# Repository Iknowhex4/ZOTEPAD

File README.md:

# ZOTEPAD

## About
This is my Zotepad it was named for Zote The Mighty from the hit indie Game 'Hollow Knight'. The Macropad has 6 keys and a rotary encoder. I designed the keys to be the battle keybinds for 'Undertale', so I can finally beat the boss Undyne the Undying. The case is a standard sandwich mount in which the PCB hangs of the top plate. The case is held together with heat set inserts and screws. I used KMK firmware to code the mapping of the keys. The case was made in onshape and the PCB has some silkcreen on it depicting the character 'Zote the Mighty'. I couldn't figure out how to hide the screws on the case; I could tell it was by flipping them upside down, but I didn't want to focus on that for my project. I found the hardest part of the project to be using CAD software for design, but after messing around a bit with the controls I figured out how to do it. I followed the guide for the begining making the PCB etc, but I stopped using it when I went back to the schematics to add my own features. 
## BOM
- 1x Zotepad Pcb
- 1x Bottom Case
- 1x Top Plate
- 6x MX Switches
- 1x Rotary Encoder EC11
- 1x XIAO RP2040
- 6x White Blank DSA keycaps
- 4x M3x16mm screws
- 4x M3x5mx4mm heatset inserts

This is my CAD link:
https://cad.onshape.com/documents/b8c557c7cba29d893ec7ee97/w/a27e70a122ce197b2fa20963/e/21f0d5da1cc23e3e0d761768?renderMode=0&uiState=6ac2b3909b3a99bbd460e99a

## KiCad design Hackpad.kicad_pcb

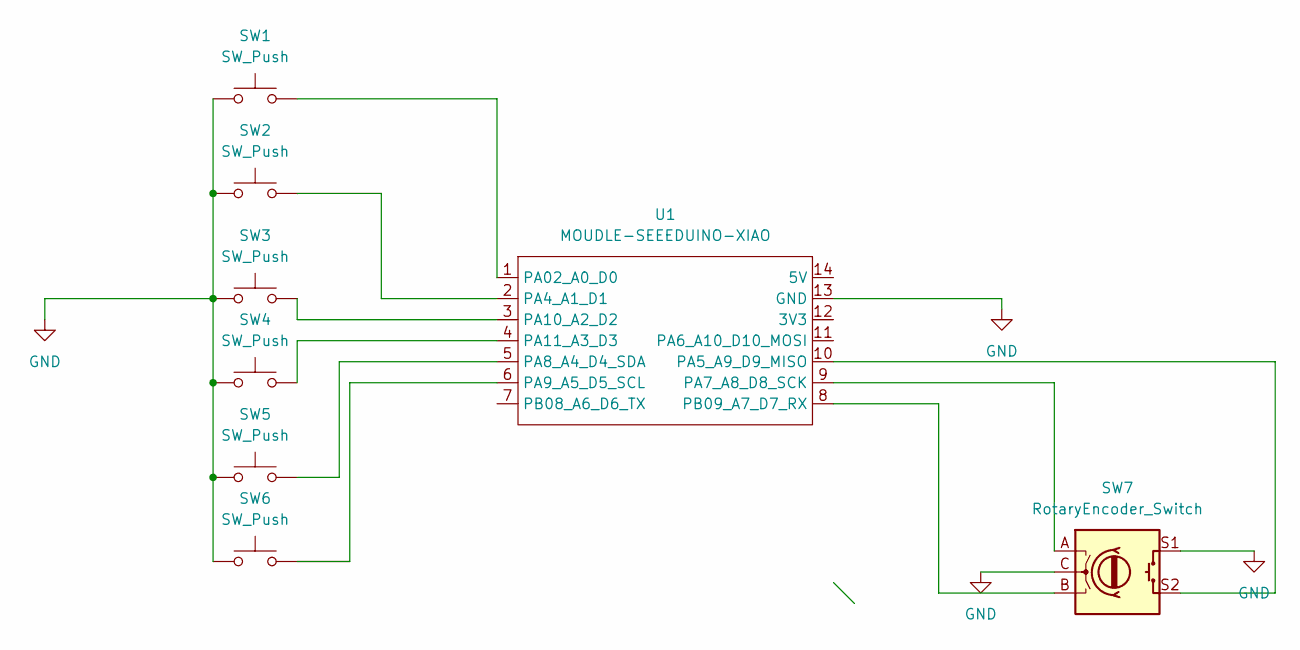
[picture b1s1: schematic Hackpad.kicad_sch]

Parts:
SW1, SW2, SW3, SW4, SW5, SW6: SW_Push
SW7: RotaryEncoder_Switch; Oscillator_SMD_ECS_2520MV-xxx-xx-4Pin_2.5x2.0mm
U1: MOUDLE-SEEEDUINO-XIAO; TQFP-44_10x10mm_P0.8mm

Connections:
GND: SW1.1, SW2.1, SW3.1, SW4.1, SW5.1, SW6.1, SW7.C, SW7.S1, U1.13 (GND)
unnamed: SW1.2, U1.1 (PA02_A0_D0)
unnamed: SW2.2, U1.2 (PA4_A1_D1)
unnamed: SW7.S2, U1.10 (PA5_A9_D9_MISO)
unnamed: SW7.A, U1.9 (PA7_A8_D8_SCK)
unnamed: SW5.2, U1.5 (PA8_A4_D4_SDA)
unnamed: SW6.2, U1.6 (PA9_A5_D5_SCL)
unnamed: SW3.2, U1.3 (PA10_A2_D2)
unnamed: SW4.2, U1.4 (PA11_A3_D3)
unnamed: SW7.B, U1.8 (PB09_A7_D7_RX)

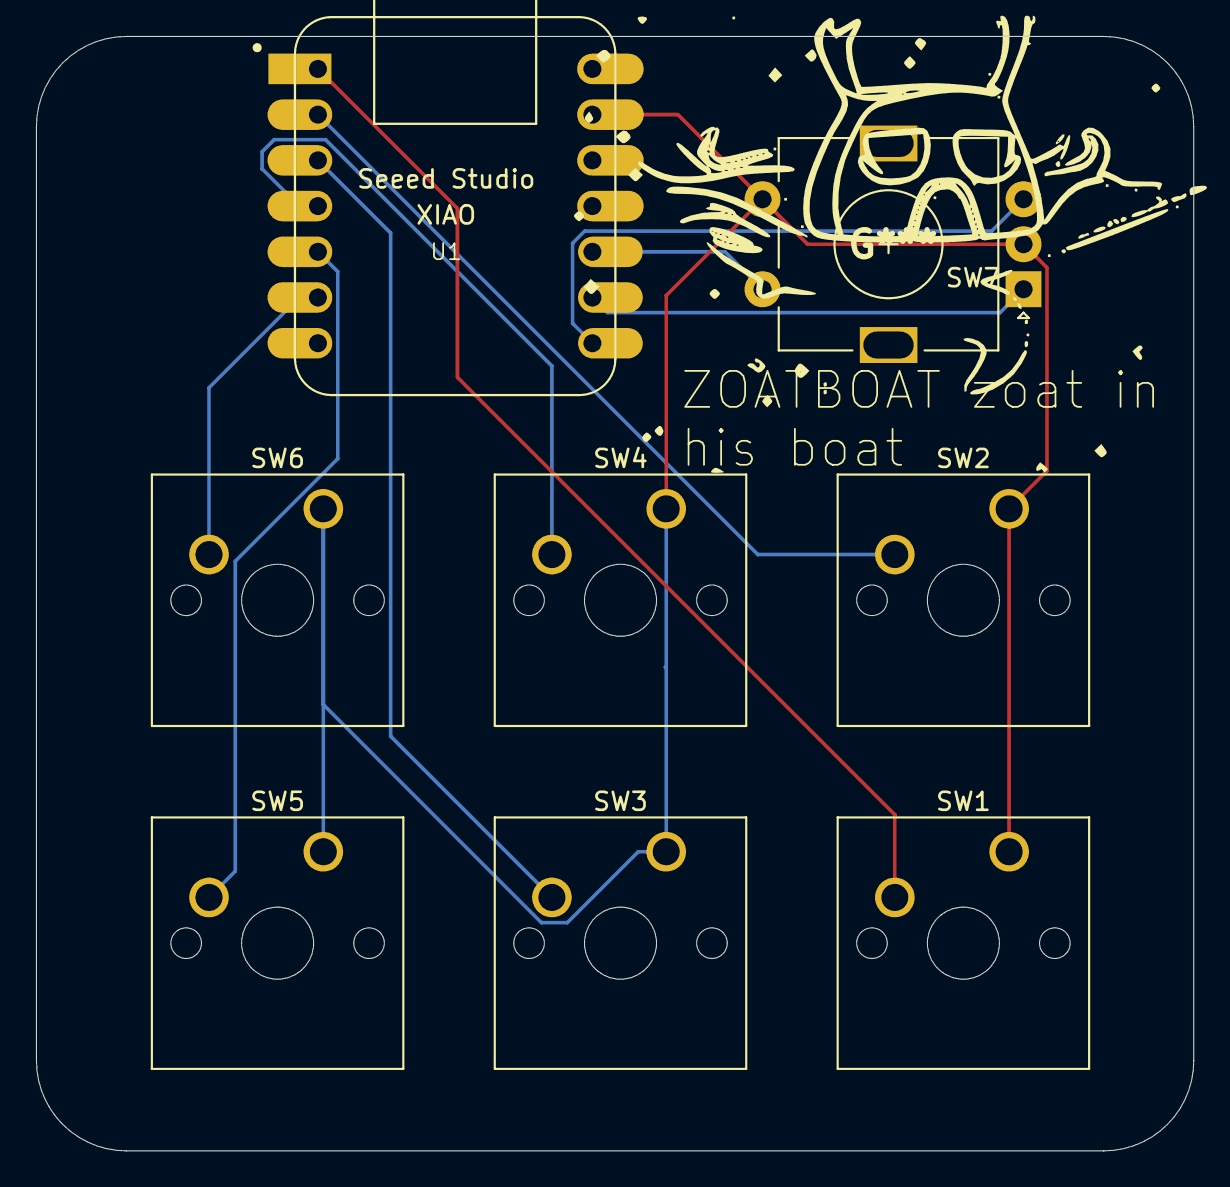
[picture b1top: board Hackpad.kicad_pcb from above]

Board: 2 copper layers, 64.3 x 61.9 mm, 8 parts (0 on the bottom side), 10 nets.
